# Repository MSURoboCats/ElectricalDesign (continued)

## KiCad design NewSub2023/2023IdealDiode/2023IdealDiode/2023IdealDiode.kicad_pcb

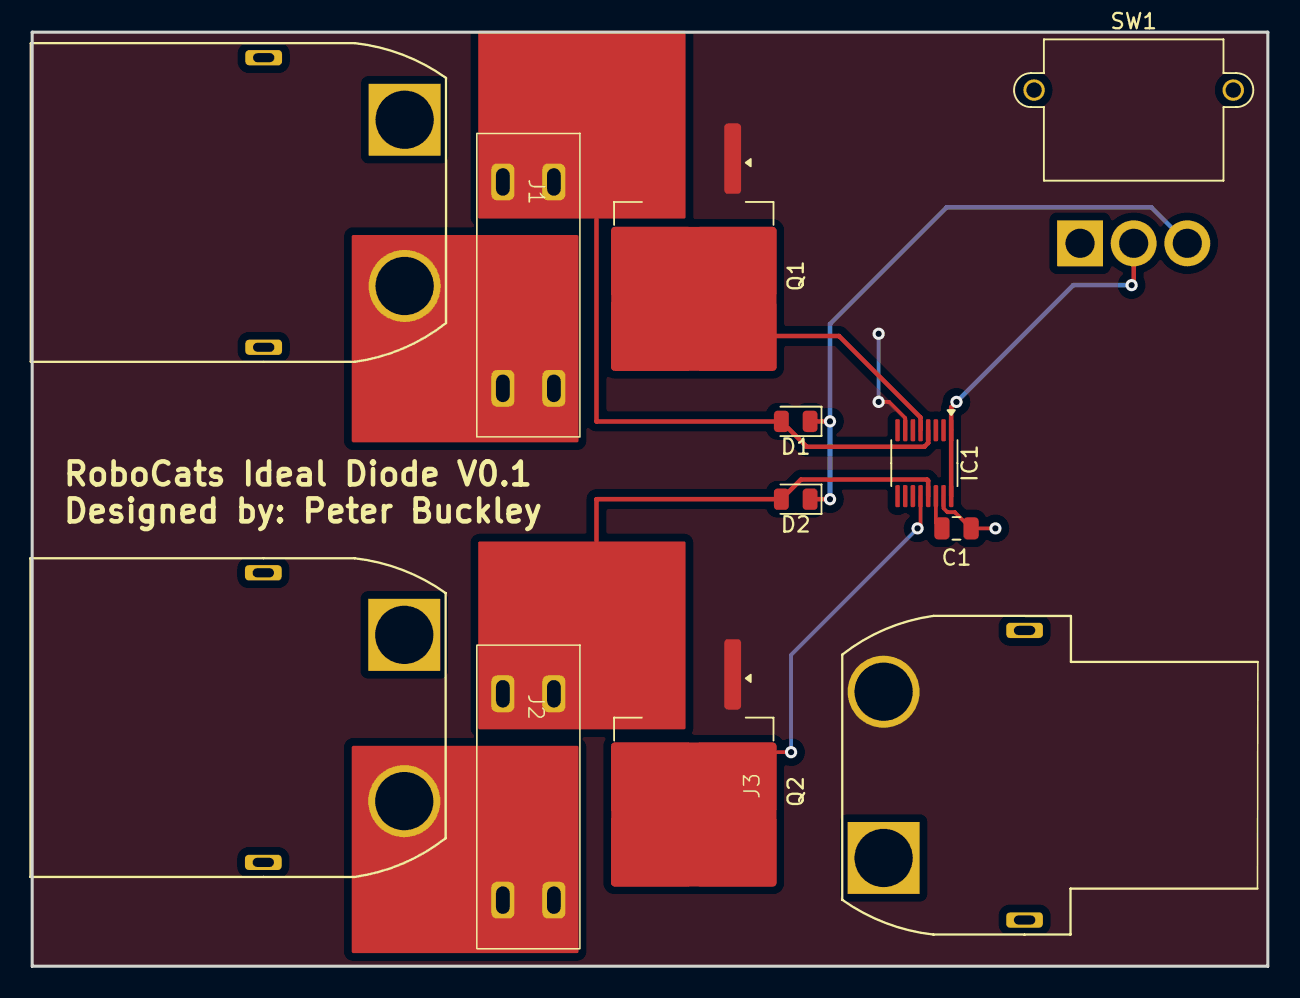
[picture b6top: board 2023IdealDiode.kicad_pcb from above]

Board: 2 copper layers, 80.6 x 61.0 mm, 12 parts (0 on the bottom side), 11 nets.

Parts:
C1: 1uF; C_0805_2012Metric
D1, D2: BAT41; D_0805_2012Metric
F1, F2: 30A; 3557-15
IC1: MSOP-16_3x4mm_P0.5mm
J1: Battery 1 Input; XT90PW-M
J2: Battery 2 Input; XT90PW-M
J3: Output; XT90PW-F
Q1, Q2: NMOS; TO-263-2
SW1: Power Switch; MR30PW-M

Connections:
GND: C1.2, IC1.15 (GND), J1.2 (-), J2.2 (-), J3.2 (-), SW1.1 (A)
unnamed: D1.2 (A), F1.1, IC1.4 (Vin2), Q1.3 (S)
unnamed: D1.1 (K), D2.1 (K), SW1.3 (C)
unnamed: D2.2 (A), F2.1, IC1.13 (Vin1), Q2.3 (S)
unnamed: IC1.1 (EN2), IC1.16 (EN1), SW1.2 (B)
unnamed: IC1.12 (GATE1), Q2.2 (G)
unnamed: IC1.5 (GATE2), Q1.2 (G)
unnamed: IC1.7 (OUT2), IC1.10 (OUT1), J3.1 (+), Q1.1 (D), Q2.1 (D)
unnamed: C1.1, IC1.14 (Vcc)
unnamed: F1.2, J1.1 (+)
unnamed: F2.2, J2.1 (+)

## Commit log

2023-10-24 Read me test push
2023-10-25 Created 2023 Power Distrobution File
2023-10-25 Testing git function
2023-10-25 Added footprints folder and test footprint
2023-11-08 Test
2023-11-08 put name in
2023-11-08 name #2
2023-11-08 Added name to Readme.txt
2023-11-08 Created MR30PW Footprint
2023-11-08 Updated Pcb Settings
2023-11-09 Added XT90PW_footprint
2023-11-30 Added Files for OldSub2022
2023-11-30 Added Ammass Footprints
2023-12-06 Created Multiple symbols and ESC footprint
2023-12-07 Finished ESC Board Footprint
2023-12-25 Added LSHD-5601 Footprint and Symbol looked at XT90PW-M footprint
2023-12-26 Added 3557-15 Footprint & Symbol Edited Br_Esc Footprint Edited XT90PW-M Footprint
2023-12-26 Added TC7107CPL Footprint & Symbol
2024-01-28 Added power block, teensy block, and 5v reg to schematic. Revised custom symbols.
2024-01-28 Resized Schematic
2024-02-01 Added 2023 Torpedo Filr Added 2023 Torpedo_Circuit_board
2024-02-02 Created Torpedo circuit schematic Created torpedo motor footprint updated torpedo circuit
2024-02-04 Matched footprints to schematic. laid out basic pcb design.
2024-02-09 Shrunk Torpedo Motor terminal Holes Shrunk Torpedo Circuit Board to 18mm Diameter Replaced Torpedo Circuit Board Power Holes with New Power Holes
2024-02-23 Complted Torpedo Board
2024-02-23 Added traces to new power distro
2024-03-01 Added "Nathaniel Oftedal v 1.0" text to Torpedo Circuit board
2024-03-01 added text to board
2024-03-01 Changed Torpedo circuit board wire thickness
2024-03-01 Split power and esc into wo projects. Revised both circuit deisgns.
2024-03-01 Added Torpedo circuit board GBR file for printing
2024-03-01 Created Gerber Files for Ideal 2023IdealDiode
2024-03-02 Finished and created gerber files for ideal diode pcb
2024-08-02 Updated Read Me File Format. Files updated to Kicad Version 8
2024-08-06 Renamed Folders
2024-09-09 Test Commit
2024-09-10 save torpedo design to new version of kicad
2024-09-30 Created Project Added Symbol Librarys
2024-10-01 Created project and librarys
2024-10-01 Made Motor Power distrobution sub Shematic
2024-10-01 Added all other motor power distribution junctions
2024-10-06 Added Jetson Orin Header Pinout
    Added symbol for Jetson AGX Orin Header Pinout
2024-10-07 Deleted copy of Jetson Header Pinout
2024-10-07 saved new symbols
2024-10-11 Added jetson pinout on to main schematic
2024-10-11 Gave motor drivers their own Power & GND
2024-10-11 save something
2024-10-11 Added pwm driver
2024-10-11 Added PCA 9862 to Power distro schematic and started PCB
2024-10-11 Created example file for version control guide
2024-10-15 Added PCA pinout schematics
2024-10-15 finish pca schematic
2024-10-15 added JST_SM06B-GHS-TB_LF__SN_ symbol and footprint into PCA pinout
2024-10-15 finished Power distro schematic
2024-10-15 Began Main IC Breakout
2024-10-15 saved i guess idk
2024-10-16 placed the footprints onto the power distro PCB and started placement
2024-10-22 Finished V1 Schematic
2024-10-22 imported symbols to PCB editor
2024-10-22 changed PowerDistro PCB to 4 layers
2024-10-29 peters yelling me
2024-10-29 Added EASYBldc Outlines
2024-10-29 Added motor controller squares
2024-10-29 Connected all pins on IMU breakout PBC editor
2024-10-29 updated lower layer to correctly cut alternative vias
2024-10-30 Added connectors and esc footprints
2024-11-03 changed motor controler numbers and hole numbers in PCB
2024-11-03 Finished V2 Torpedos
2024-11-05 rearranged the power distro board
2024-11-07 layed out the first set of traces for motor drivers
2024-11-13 Created 3d Model
2024-11-15 saving new power distro orientation
2024-11-15 Pushing so Power connector can be added
2024-11-15 renamed the motor controllers
2024-11-18 Added Vertical Connector Footprints, Fixed MR-30 symbol
2024-11-19 add XT-90PB
2024-11-19 Added power layer to power distro motors
2024-11-26 wired the PCA and Orin connecter together and added motor controller comms
2024-11-27 saved the 2023 version of the solidworks board
2024-12-23 Fixed 3d models
2025-03-12 Created Battery Protection Project
2025-03-12 i dont know
2025-03-13 started working on a latch for the battery protection board
2025-03-13 autosave
2025-03-19 Designed a working version for the Protection circuit
2025-03-19 No Idea what that stuff is
2025-03-19 Latching design created
2025-03-25 complete circuit
2025-03-25 Added components to schematic
2025-03-25 started Kicad Schematic
2025-03-25 Started on PCB
2025-03-26 tried saving again
2025-03-27 Added ldo and comparitors
2025-03-27 Made it to help peters sanity
2025-03-27 finished the circuit again
2025-03-29 Added connectors
2025-03-29 changed transistors
2025-03-29 updated small bits in LTS and Kicad schematics
2025-03-29 started PCB layout
2025-03-29 redrew PCB
2025-03-31 different design on PCB uploaded
2025-03-31 missing one more wire
2025-04-06 Made a complete PCB design
2025-04-10 more work on PCB
2025-04-10 more edits
2025-04-15 DID the voltage protection PCB
2025-04-15 little more
2025-04-15 a;sldjfhalkshf
2025-04-23 Changed Everything
2025-04-24 Release
2025-04-26 fixed a tiny trace issue
2025-05-04 nothing important
2025-05-19 nothing
2025-06-06 nada
2025-08-26 nuh uh
2025-09-16 idk man
2026-02-07 not much
2026-02-07 Got rid of peter's "did poorly statement"
2026-02-07 Added Switch to Bat Protect Board
2026-03-06 Files for printing PCB
2026-03-10 created Project for Documentation
